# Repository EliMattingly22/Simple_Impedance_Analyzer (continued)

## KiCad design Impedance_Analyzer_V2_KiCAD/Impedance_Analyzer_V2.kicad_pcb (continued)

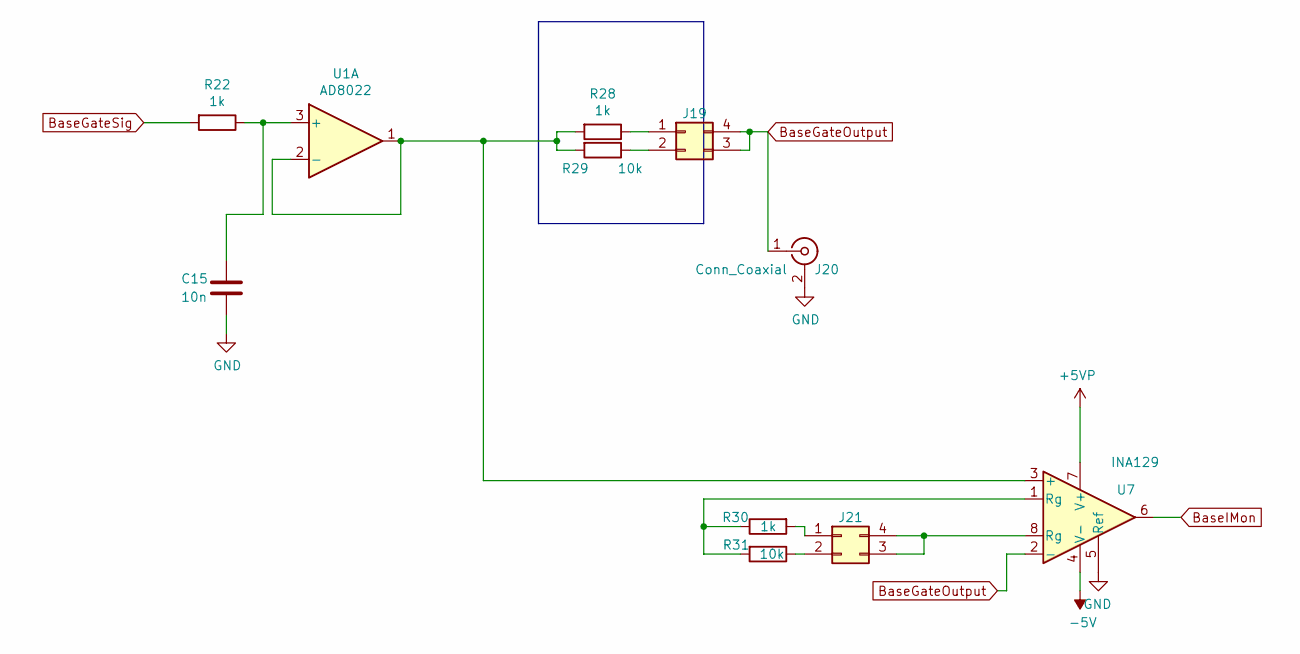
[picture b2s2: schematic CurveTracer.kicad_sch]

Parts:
C15: 10n; C_0805_2012Metric
J19, J21: Conn_02x02_Counter_Clockwise; PinHeader_2x02_P2.54mm_Vertical
J20: Conn_Coaxial; 31-5486-1010 BNC Panel RA
R22, R28, R30: 1k; R_1206_3216Metric
R29, R31: 10k; R_1206_3216Metric
U1: AD8022; SO-8_3.9x4.9mm_P1.27mm
U7: INA129; DIP-8_W7.62mm

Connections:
+5VP: U7.7 (V+); also elsewhere on the board
-5V: U7.4 (V-); also elsewhere on the board
BaseGateOutput: J19.3, J19.4, J20.1 (In), U7.2 (-)
BaseGateSig: R22.2; also elsewhere on the board
BaseIMon: U7.6; also elsewhere on the board
GND: C15.2, J20.2 (Ext), U7.5 (Ref); also elsewhere on the board
unnamed: C15.1, R22.1, U1.3 (+)
unnamed: J19.1, R28.1
unnamed: J19.2, R29.1
unnamed: J21.1, R30.2
unnamed: J21.2, R31.1
unnamed: J21.3, J21.4, U7.8 (Rg)
unnamed: R28.2, R29.2, U1.1, U1.2 (-), U7.3 (+)
unnamed: R30.1, R31.2, U7.1 (Rg)

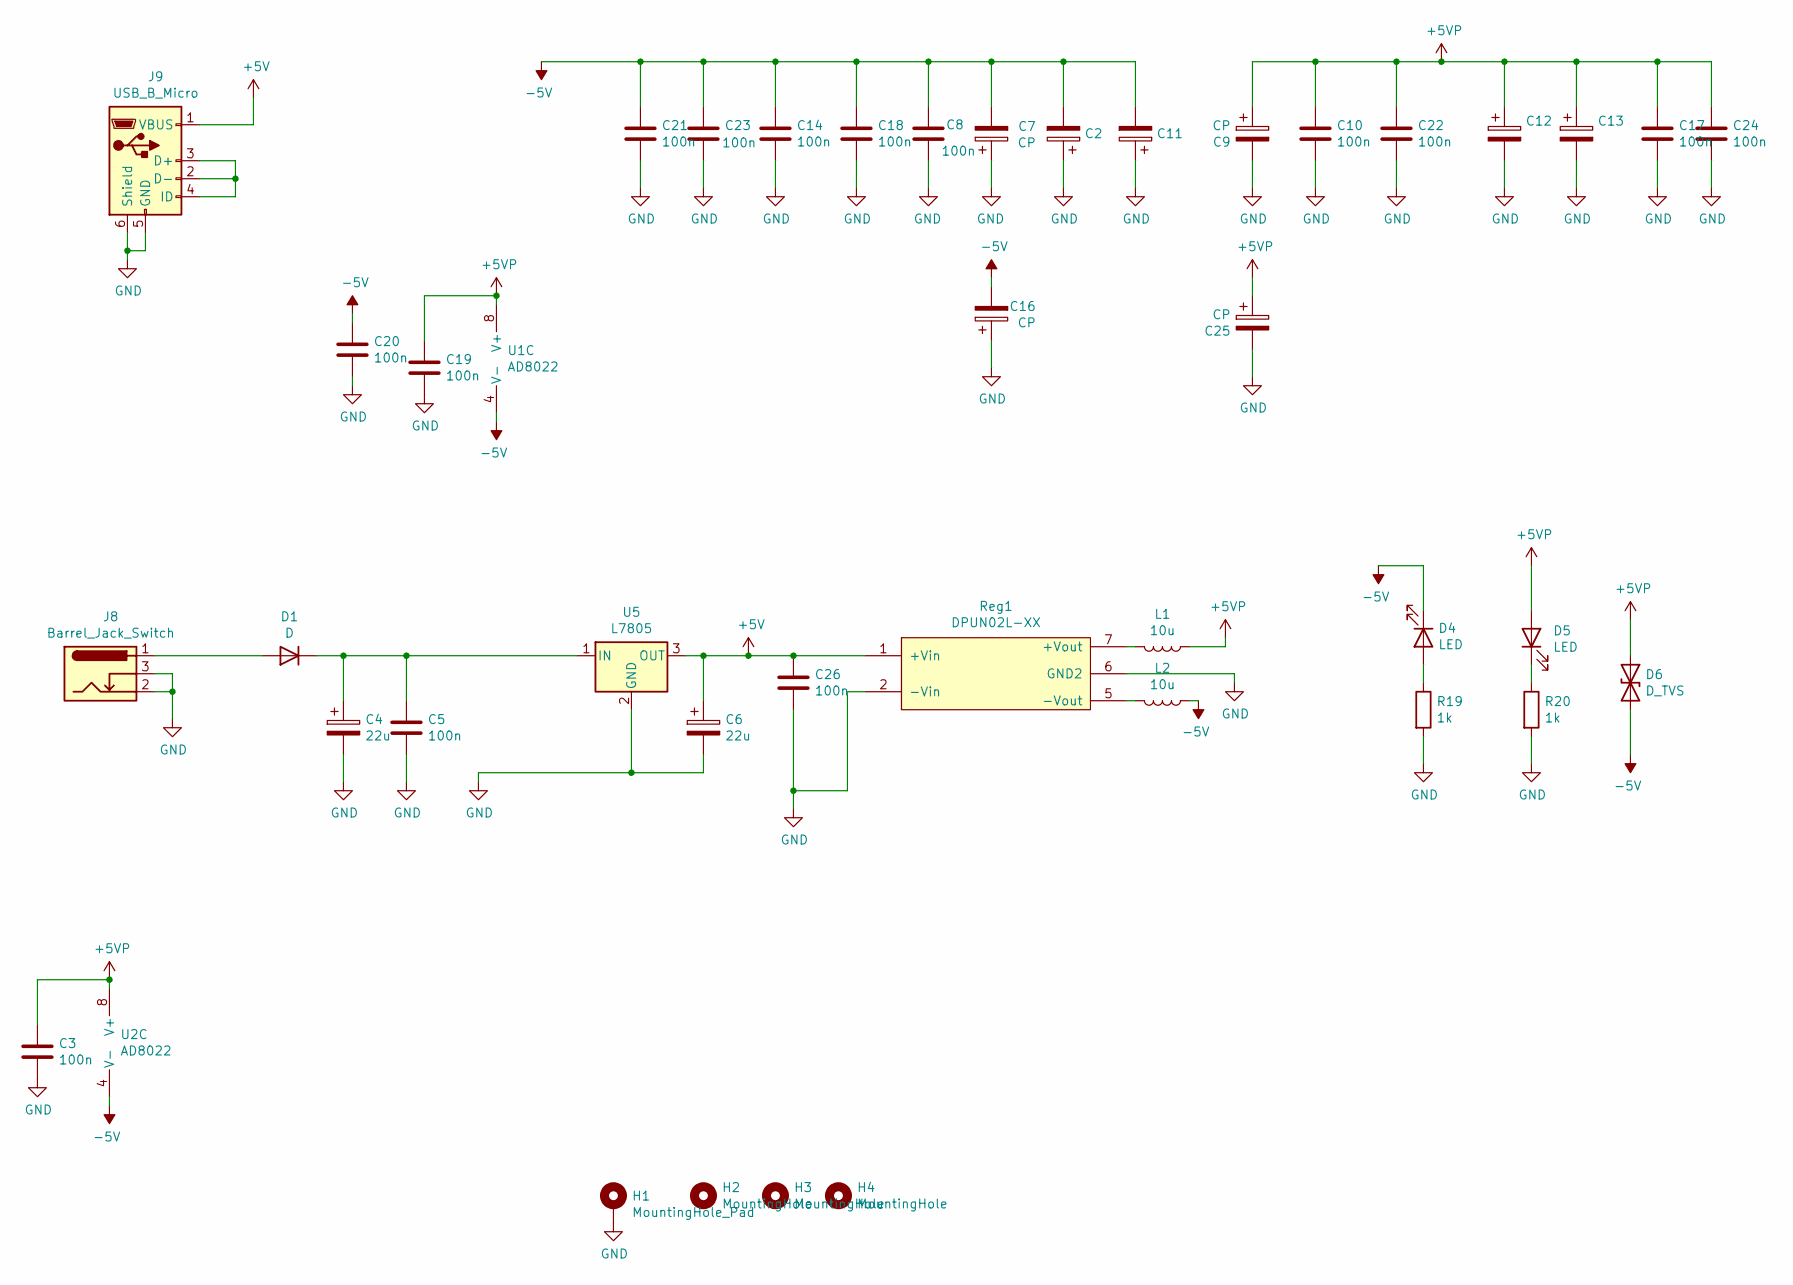
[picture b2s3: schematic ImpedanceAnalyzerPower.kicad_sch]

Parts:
C2, C11, C12, C13: C_Polarized; C_1206_3216Metric_Pad1.33x1.80mm_HandSolder
C3, C5, C8, C10, C14, C17, C18, C19, C20, C21, C22, C23, C24, C26: 100n; C_0805_2012Metric
C4, C6: 22u; CP_Radial_D5.0mm_P2.00mm
C7, C9, C16, C25: CP; CP_Radial_D8.0mm_P5.00mm
D1: D; D_SMA
D4, D5: LED; LED_1206_3216Metric
D6: D_TVS; D_SMA
H1: MountingHole_Pad; MountingHole_4.3mm_M4_Pad
H2, H3, H4: MountingHole; MountingHole_4mm
J8: Barrel_Jack_Switch; BarrelJack_Horizontal
J9: USB_B_Micro; USB_Micro-B_Wuerth_629105150521
L1, L2: 10u; L_Taiyo-Yuden_NR-60xx_HandSoldering
R19, R20: 1k; R_1206_3216Metric
Reg1: DPUN02L-XX; SIP-2W-7
U1, U2: AD8022; SO-8_3.9x4.9mm_P1.27mm
U5: L7805; TO-220-3_Vertical

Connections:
+5V: C6.1, C26.1, J9.1 (VBUS), Reg1.1 (+Vin), U5.3 (OUT)
+5VP: C3.1, C9.1, C10.1, C12.1, C13.1, C17.1, C19.1, C22.1, C24.1, C25.1, D5.2 (A), D6.1 (A1), L1.1, U1.8 (V+), U2.8 (V+); also elsewhere on the board
-5V: C2.2, C7.2, C8.1, C11.2, C14.1, C16.2, C18.1, C20.1, C21.1, C23.1, D4.1 (K), D6.2 (A2), L2.1, U1.4 (V-), U2.4 (V-); also elsewhere on the board
GND: C2.1, C3.2, C4.2, C5.2, C6.2, C7.1, C8.2, C9.2, C10.2, C11.1, C12.2, C13.2, C14.2, C16.1, C17.2, C18.2, C19.2, C20.2, C21.2, C22.2, C23.2, C24.2, C25.2, C26.2, H1.1, J8.2, J8.3, J9.5 (GND), J9.6 (Shield), R19.2, R20.2, Reg1.2 (-Vin), Reg1.6 (GND2), U5.2 (GND); also elsewhere on the board
unnamed: C4.1, C5.1, D1.1 (K), U5.1 (IN)
unnamed: D1.2 (A), J8.1
unnamed: D4.2 (A), R19.1
unnamed: D5.1 (K), R20.1
unnamed: J9.2 (D-), J9.3 (D+), J9.4 (ID)
unnamed: L1.2, Reg1.7 (+Vout)
unnamed: L2.2, Reg1.5 (-Vout)

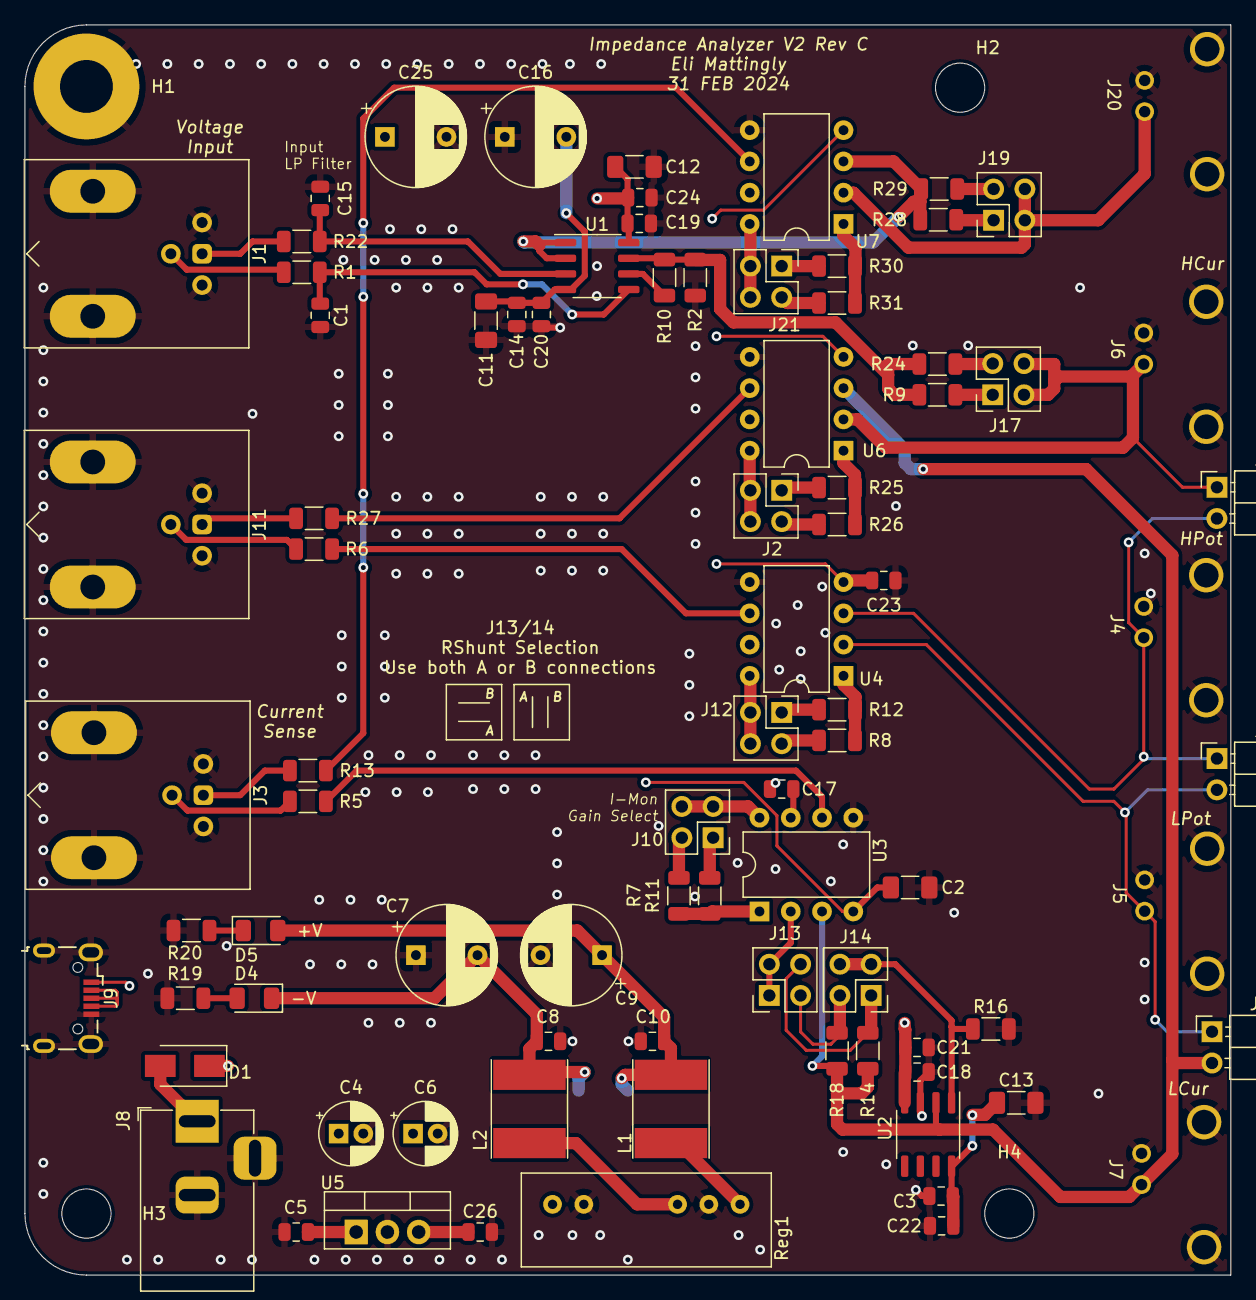
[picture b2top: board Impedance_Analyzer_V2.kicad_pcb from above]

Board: 4 copper layers, 98.0 x 101.6 mm, 90 parts (1 on the bottom side), 55 nets.

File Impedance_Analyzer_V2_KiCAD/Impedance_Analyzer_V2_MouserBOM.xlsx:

Comment | Designator | Footprint | Mouser PN
BUF634 | BUF1,BUF2 | Package_SO:SO-8_3.9x4.9mm_P1.27mm | 595-BUF634AIDR
1n | C1,C15 | Capacitor_SMD:C_0805_2012Metric
10n | C16,C25 | Capacitor_SMD:C_0805_2012Metric
C_Polarized | C2,C11,C12,C13 | Capacitor_SMD:C_1206_3216Metric_Pad1.33x1.80mm_HandSolder | 603-CC126KKX7R8BB106
100n | C3,C5,C8,C10,C14,C17,C18,C19,C20,C21,C22,C23,C24 | Capacitor_SMD:C_0805_2012Metric
22u | C4,C6 | Capacitor_THT:CP_Radial_D5.0mm_P2.00mm | 710-860010372006
CP | C7,C9 | Capacitor_THT:CP_Radial_D8.0mm_P5.00mm | 667-ECA-1CM331B
D | D1 | Diode_SMD:D_SMA
D_TVS | D2,D6 | Diode_SMD:D_SMA | 621-SMAJ18CA-13-F
LED | D3,D4,D5 | LED_SMD:LED_1206_3216Metric
Ferrite_Bead | FB1 | Resistor_SMD:R_0805_2012Metric
MountingHole_Pad | H1 | MountingHole:MountingHole_4.3mm_M4_Pad
MountingHole | H2,H3,H4 | MountingHole:MountingHole_4mm
Conn_Coaxial | J1,J2,J3,J4,J5,J6,J7 | Connector_Coaxial:BNC_TEConnectivity_1478204_Vertical | 571-413631-1
Conn_02x02_Counter_Clockwise | J10,J12,J13,J14,J15,J16,J17 | Connector_PinHeader_2.54mm:PinHeader_2x02_P2.54mm_Vertical | 855-M20-9980245
Screw_Terminal_01x03 | J11 | TerminalBlock:TerminalBlock_bornier-3_P5.08mm
Barrel_Jack_Switch | J8 | Connector_BarrelJack:BarrelJack_Horizontal
USB_B_Micro | J9 | Connector_USB:USB_Micro-B_Wuerth_629105150521 | 710-629105150521
10u | L1,L2 | Inductor_SMD:L_Taiyo-Yuden_NR-60xx_HandSoldering | 963-NR6045T100M
1k | R1,R11,R12,R13,R19,R20,R22 | Resistor_SMD:R_1206_3216Metric
0 | R10 | Resistor_SMD:R_1206_3216Metric
50 | R15,R17 | Resistor_SMD:R_1206_3216Metric
10k | R2,R7,R8,R14,R16,R24 | Resistor_SMD:R_1206_3216Metric | 284-APC1206B10K0N
DNP | R3,R4,R21,R23 | Resistor_SMD:R_1206_3216Metric
47 | R5,R6 | Resistor_SMD:R_1206_3216Metric
100 | R9,R18 | Resistor_SMD:R_1206_3216Metric | 71-TNPW1206100RBYEN
DPUN02L-XX | Reg1 | Martinos:SIP-2W-7 | 709-DPUN02L-05
OPA2830 | U1,U2 | Package_SO:SO-8_3.9x4.9mm_P1.27mm | 595-OPA2830IDR
INA121 | U3,U4 | Package_DIP:DIP-8_W7.62mm | 595-INA121PA
L7805 | U5 | Package_TO_SOT_THT:TO-220-3_Vertical
Shorting pins | Order 10+ |  | 571-28815452

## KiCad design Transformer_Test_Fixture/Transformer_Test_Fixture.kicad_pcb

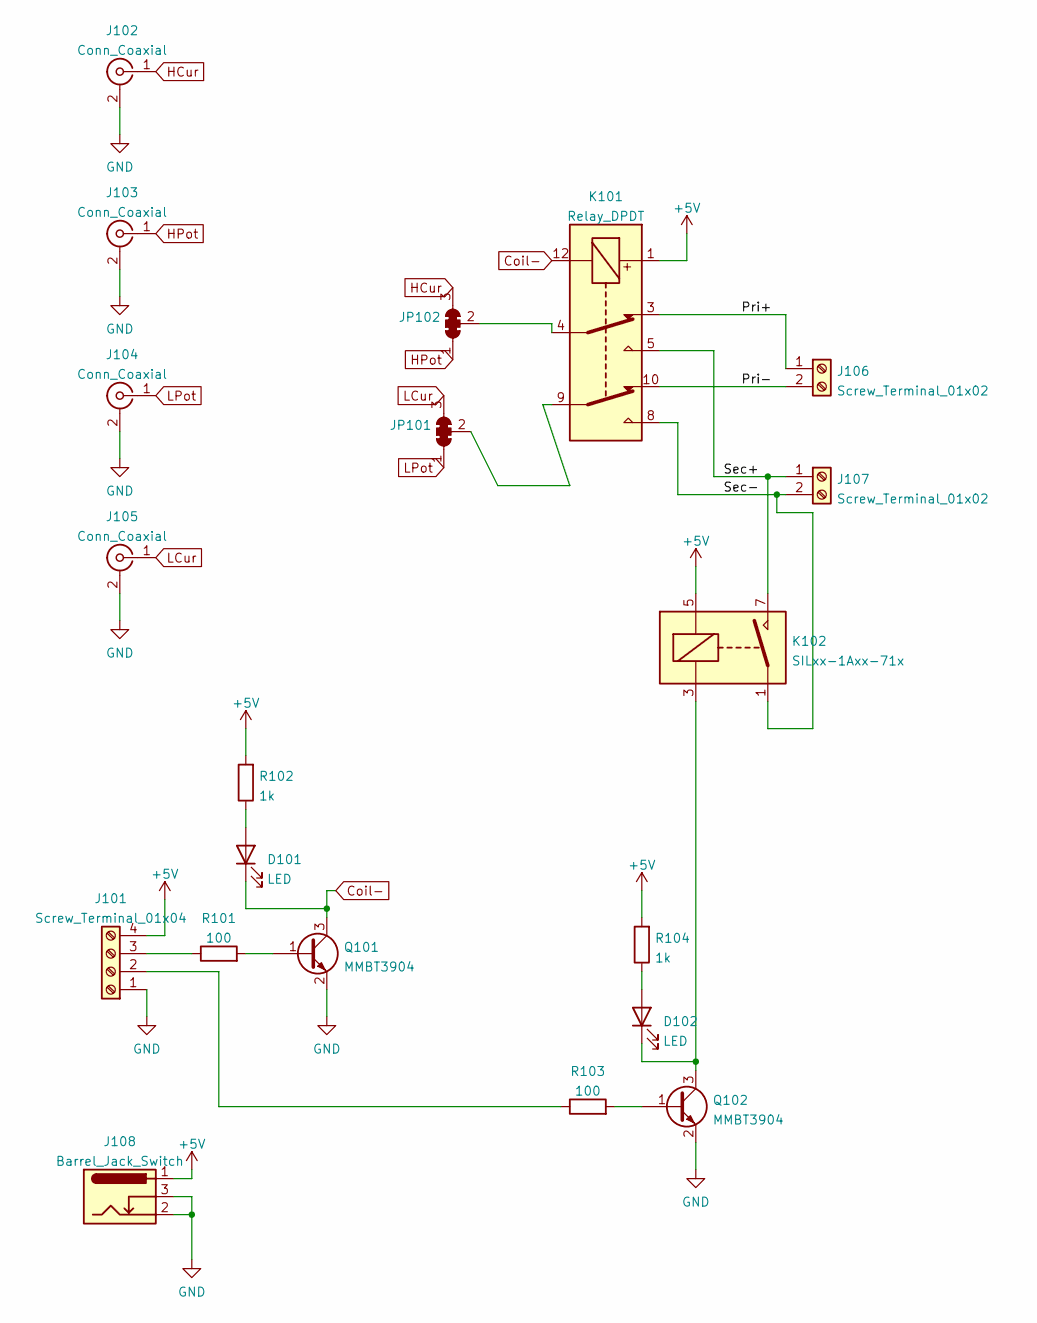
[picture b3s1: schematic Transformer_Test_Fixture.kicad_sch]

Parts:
D101, D102: LED; LED_0805_2012Metric_Pad1.15x1.40mm_HandSolder
J101: Screw_Terminal_01x04; TerminalBlock_bornier-4_P5.08mm
J102, J103, J104, J105: Conn_Coaxial; BNC_Amphenol_B6252HB-NPP3G-50_Horizontal
J106, J107: Screw_Terminal_01x02; TerminalBlock_bornier-2_P5.08mm
J108: Barrel_Jack_Switch; BarrelJack_GCT_DCJ200-10-A_Horizontal
JP101, JP102: SolderJumper_3_Bridged123; SolderJumper-3_P1.3mm_Bridged12_RoundedPad1.0x1.5mm
K101: Relay_DPDT; Relay_DPDT_Omron_G6S-2
K102: SILxx-1Axx-71x; Relay_SPST_StandexMeder_SIL_Form1A
Q101, Q102: MMBT3904; SOT-23
R101, R103: 100; R_0805_2012Metric
R102, R104: 1k; R_0805_2012Metric

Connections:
+5V: J101.4, J108.1, K101.1, K102.5, R102.2, R104.2
/Pri+: J106.1, K101.3
/Pri-: J106.2, K101.10
/Sec+: J107.1, K101.5, K102.7
/Sec-: J107.2, K101.8, K102.1
Coil-: D101.1 (K), K101.12, Q101.3 (C)
GND: J101.1, J102.2 (Ext), J103.2 (Ext), J104.2 (Ext), J105.2 (Ext), J108.2, J108.3, Q101.2 (E), Q102.2 (E)
HCur: J102.1 (In), JP102.3 (B)
HPot: J103.1 (In), JP102.1 (A)
LCur: J105.1 (In), JP101.3 (B)
LPot: J104.1 (In), JP101.1 (A)
unnamed: D101.2 (A), R102.1
unnamed: D102.1 (K), K102.3, Q102.3 (C)
unnamed: D102.2 (A), R104.1
unnamed: JP101.2 (C), K101.9
unnamed: JP102.2 (C), K101.4
unnamed: Q101.1 (B), R101.2
unnamed: Q102.1 (B), R103.2
unnamed: J101.3, R101.1
unnamed: J101.2, R103.1

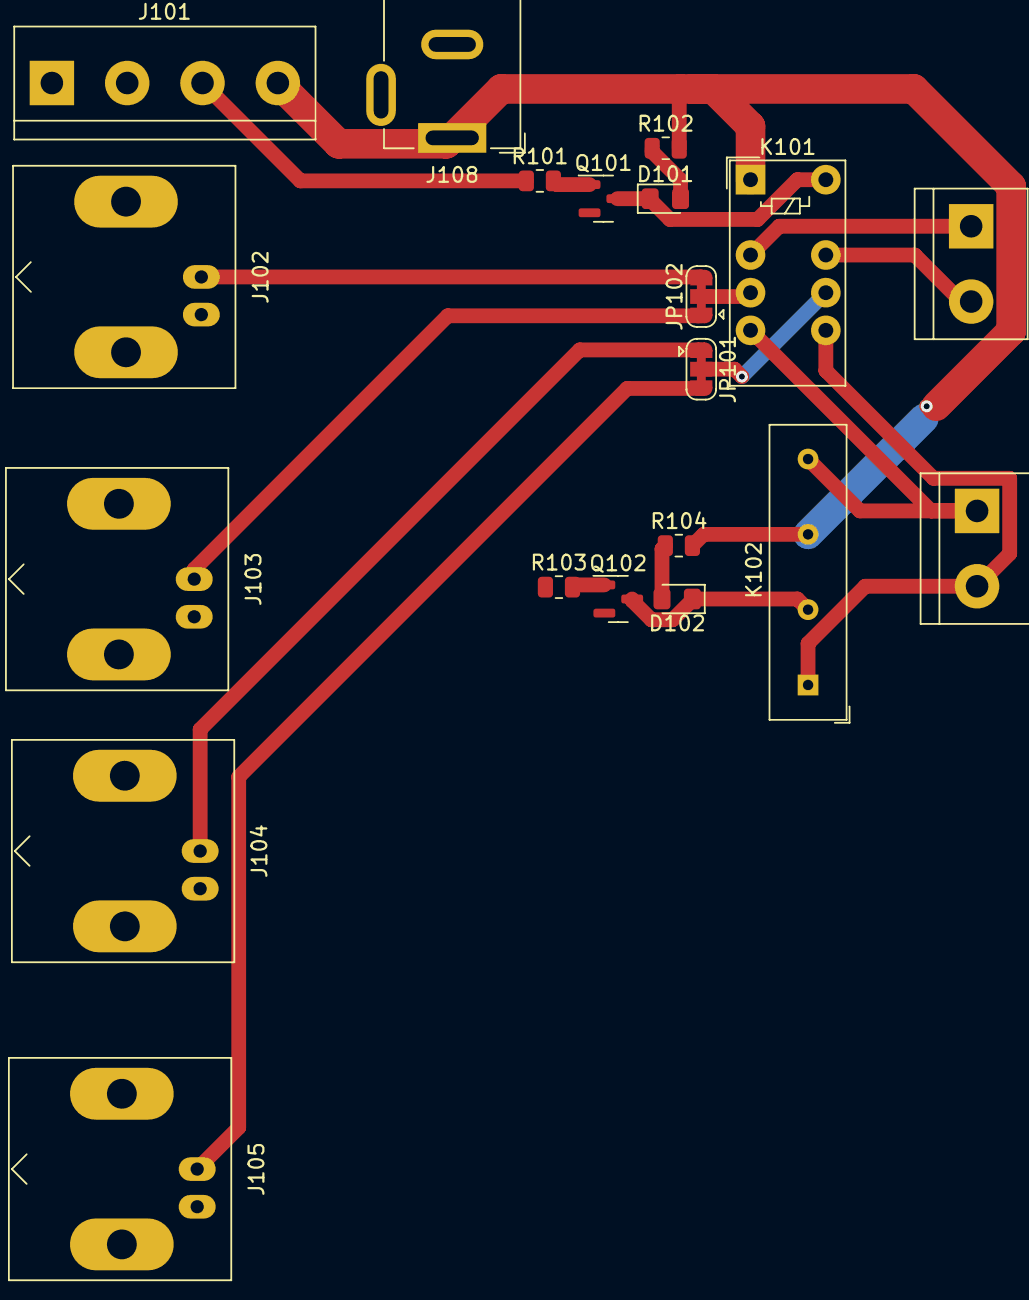
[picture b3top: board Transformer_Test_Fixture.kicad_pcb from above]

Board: 2 copper layers, 20 parts (0 on the bottom side), 20 nets.

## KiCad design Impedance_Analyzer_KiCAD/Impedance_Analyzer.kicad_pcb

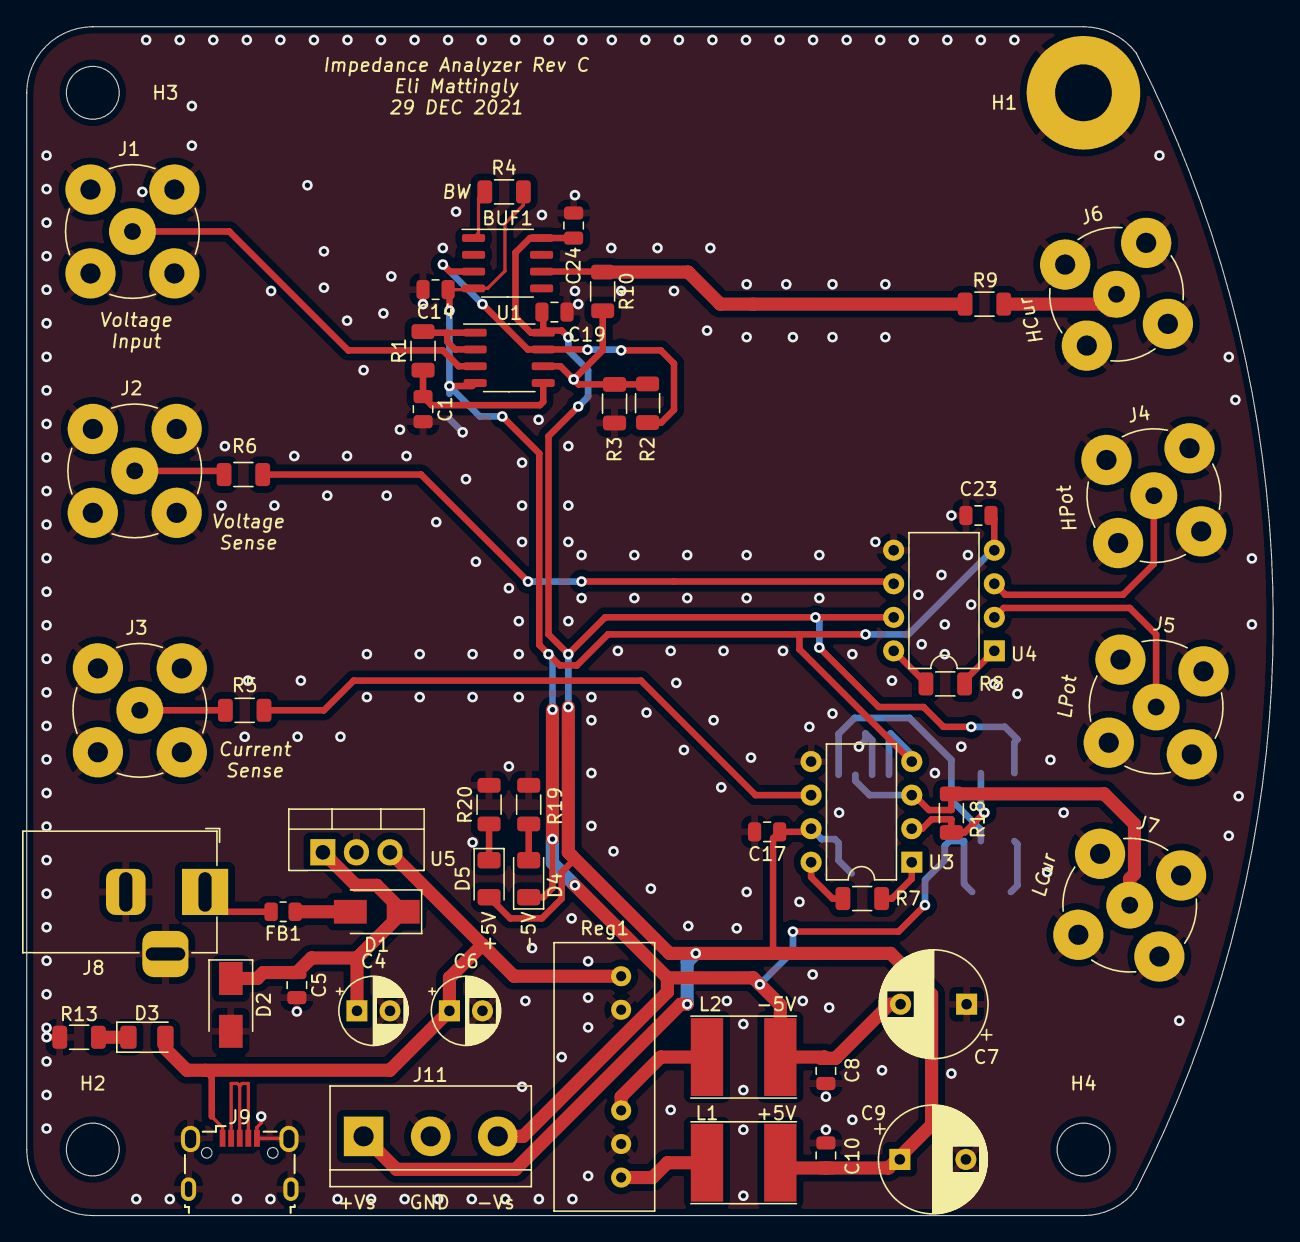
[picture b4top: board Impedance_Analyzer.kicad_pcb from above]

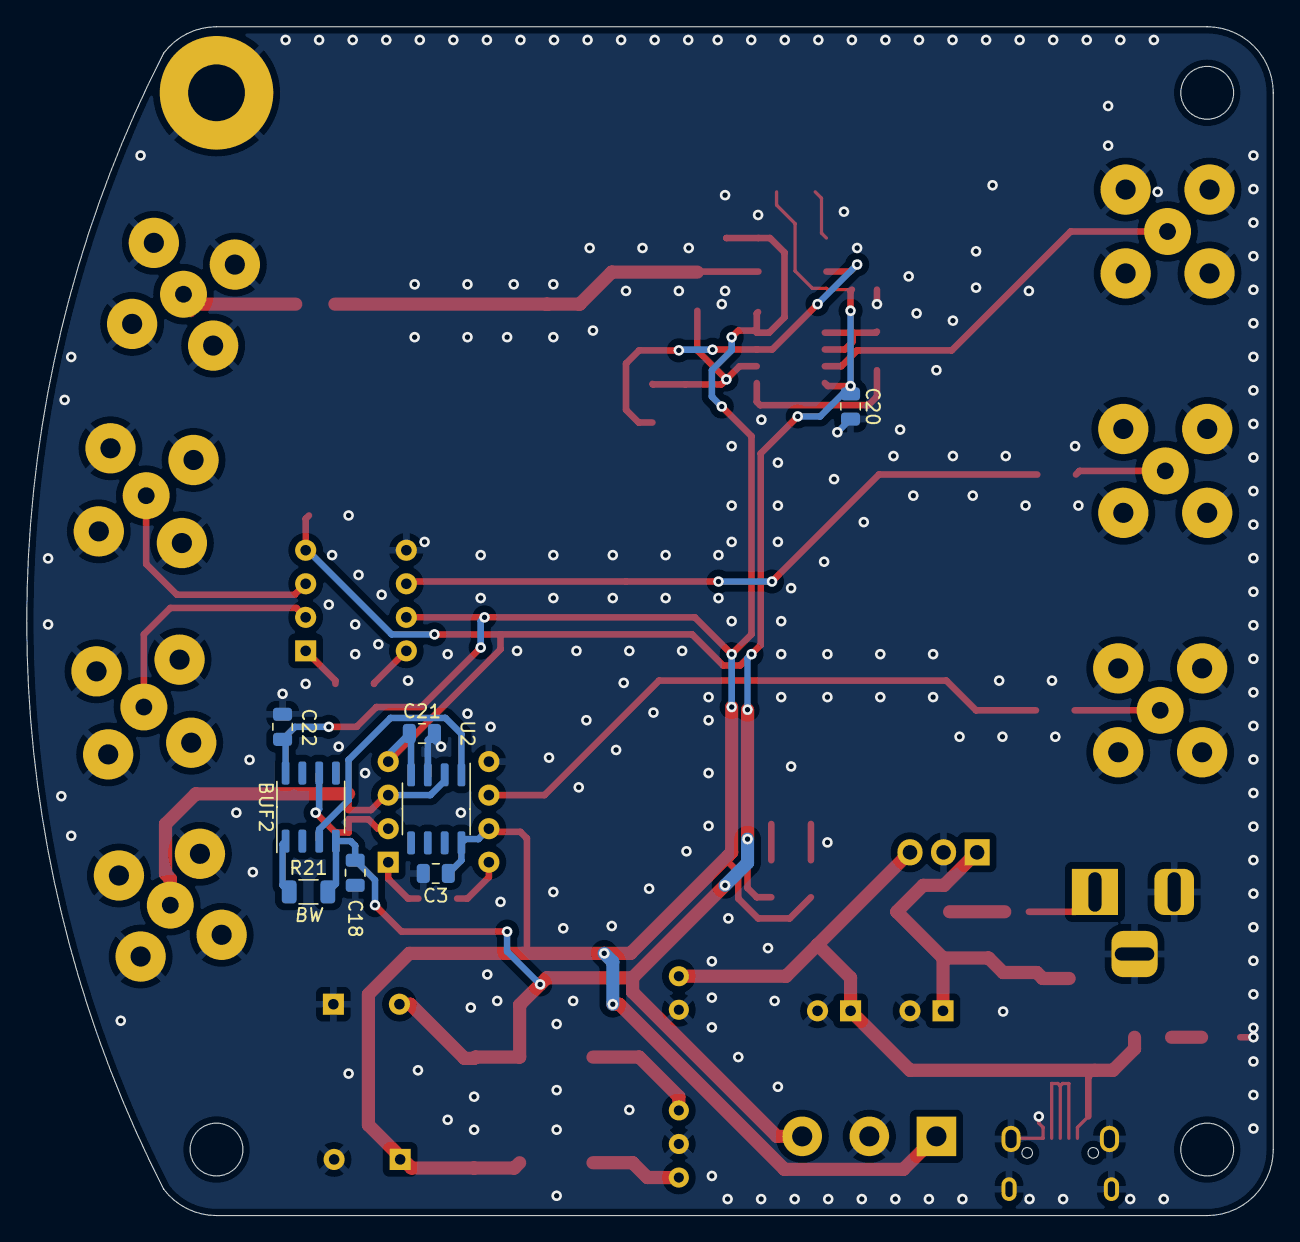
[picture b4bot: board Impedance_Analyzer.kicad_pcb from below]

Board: 2 copper layers, 94.4 x 90.0 mm, 63 parts (8 on the bottom side), 35 nets.

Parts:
BUF1, BUF2: BUF634; SO-8_3.9x4.9mm_P1.27mm
C1: 1n; C_0805_2012Metric
C3, C5, C8, C10, C14, C17, C18, C19, C20, C21, C22, C23, C24: 100n; C_0805_2012Metric
C4, C6: 22u; CP_Radial_D5.0mm_P2.50mm
C7, C9: CP; CP_Radial_D8.0mm_P5.00mm
D1: D; D_SMA
D2: D_TVS; D_SMA
D3, D4, D5: LED; LED_1206_3216Metric
FB1: Ferrite_Bead; R_0805_2012Metric
H1: MountingHole_Pad; MountingHole_4.3mm_M4_Pad
H2, H3, H4: MountingHole; MountingHole_4mm
J1, J2, J3, J4, J5, J6, J7: Conn_Coaxial; BNC_TEConnectivity_1478204_Vertical
J8: Barrel_Jack_Switch; BarrelJack_Horizontal
J9: USB_B_Micro; USB_Micro-B_Wuerth_629105150521
J11: Screw_Terminal_01x03; TerminalBlock_bornier-3_P5.08mm
L1, L2: 10u; L_Taiyo-Yuden_NR-60xx_HandSoldering
R1, R13, R19, R20: 1k; R_1206_3216Metric
R2, R10: 0; R_1206_3216Metric
R3, R4, R21: DNP; R_1206_3216Metric
R5, R6: 47; R_1206_3216Metric
R7, R8: 10k; R_1206_3216Metric
R9, R18: 100; R_1206_3216Metric
Reg1: DPUN02L-XX; SIP-2W-7
U1, U2: LM358; SO-8_3.9x4.9mm_P1.27mm
U3, U4: INA129; DIP-8_W7.62mm
U5: L7805; TO-220-3_Vertical

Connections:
+5V: C6.1, D3.2 (A), J9.1 (VBUS), Reg1.1 (+Vin), U5.3 (OUT)
+5VP: BUF1.8 (V+), BUF2.8 (V+), C3.1, C9.1, C10.1, C17.1, C19.1, C22.1, C24.1, D5.2 (A), J11.1, L1.1, U1.8 (V+), U2.8 (V+), U3.7 (V+), U4.7 (V+)
-5V: BUF1.4 (V-), BUF2.4 (V-), C7.2, C8.1, C14.1, C18.1, C20.1, C21.1, C23.1, D4.1 (K), J11.3, L2.1, R4.2, R21.2, U1.4 (V-), U2.4 (V-), U3.4 (V-), U4.4 (V-)
GND: C1.2, C3.2, C4.2, C5.2, C6.2, C7.1, C8.2, C9.2, C10.2, C14.2, C17.2, C18.2, C19.2, C20.2, C21.2, C22.2, C23.2, C24.2, D2.2 (A2), H1.1, J1.2 (Ext), J2.2 (Ext), J3.2 (Ext), J4.2 (Ext), J5.2 (Ext), J6.2 (Ext), J7.2 (Ext), J8.2, J8.3, J9.5 (GND), J9.6 (Shield), J11.2, R3.2, R13.2, R19.2, R20.2, Reg1.2 (-Vin), Reg1.6 (GND2), U2.3 (+), U3.5 (Ref), U4.5 (Ref), U5.2 (GND)
IMon+: J7.1 (In), R18.2, U2.2 (-), U3.3 (+)
IMon-: BUF2.6 (Out), R18.1, U3.2 (-)
IOut: J6.1 (In), R9.1
unnamed: BUF1.1 (BW), R4.1
unnamed: BUF1.3 (In), R2.1, U1.7
unnamed: BUF1.6 (Out), R9.2, R10.1
unnamed: BUF2.1 (BW), R21.1
unnamed: BUF2.3 (In), U2.1
unnamed: C1.1, R1.1, U1.5 (+)
unnamed: C4.1, C5.1, D1.1 (K), D2.1 (A1), U5.1 (IN)
unnamed: D1.2 (A), FB1.1
unnamed: D3.1 (K), R13.1
unnamed: D4.2 (A), R19.1
unnamed: D5.1 (K), R20.1
unnamed: FB1.2, J8.1
unnamed: J1.1 (In), U1.3 (+)
unnamed: J2.1 (In), R6.2
unnamed: J3.1 (In), R5.2
unnamed: J4.1 (In), U4.3 (+)
unnamed: J5.1 (In), U4.2 (-)
unnamed: J9.2 (D-), J9.3 (D+), J9.4 (ID)
unnamed: L1.2, Reg1.7 (+Vout)
unnamed: L2.2, Reg1.5 (-Vout)
unnamed: R1.2, U1.1, U1.2 (-)
unnamed: R5.1, U3.6
unnamed: R6.1, U4.6
unnamed: R7.1, U3.8 (Rg)
unnamed: R7.2, U3.1 (Rg)
unnamed: R8.1, U4.1 (Rg)
unnamed: R8.2, U4.8 (Rg)
unnamed: R2.2, R3.1, R10.2, U1.6 (-)

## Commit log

2021-12-25 Initialize
2021-12-26 Formatting, Minor fixes
2021-12-30 Update LTSPICE, Minor board changes
2022-01-03 Add labview
2022-01-04 Add Stats
2022-01-04 Save for prev Labview version
2022-01-04 Update for computer
2022-01-07 Add saving - bundle data
2022-01-08 Organize front panel
2022-01-08 Initial Julia Unpacking Functions
2022-01-08 Plotting and add CPar/RPar
2022-01-10 Save for V20
2022-01-10 Update Defaults and example data
2022-01-11 Gerbers
2022-01-14 Update v20
2022-01-14 upgrade v20 to 2021
2022-01-14 Accuracy testing
2022-01-15 Main operation GUI
2022-02-04 Update system
2022-08-01 V2Rev B update schematic and add V3 folder
2022-08-14 Add BOM, update readme
2022-08-18 labview updates
2022-08-23 ScreenShots
2022-08-24 Add STEP file, minor changes
2022-08-24 Add case
2022-09-02 Add Resistor Accuracy Testing
2022-09-04 Collect Accuracy Data
2022-09-04 Process data, make figs
2022-09-05 Add load compensation, reacquire data
2022-09-05 Meas capacitors
2022-09-05 Update readme, comment in schematic
2022-09-06 Add PDF schematic
2022-10-06 Bug fix, cluster size
2024-03-03 Make Rev C + Curve tracer init
2024-04-28 Update Impedance board
2024-07-04 Initial Labview update
